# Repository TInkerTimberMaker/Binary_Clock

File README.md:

# Arduino Binary Clock (3× 74HC595 + DS3231)

A friendly, buildable binary‑coded decimal (BCD) clock for the Arduino Nano. It drives **three chained 74HC595 shift registers** in **sink mode** to show **hours, minutes, seconds**. A **DS3231 RTC** provides accurate timekeeping; two buttons set the time; a pot on **A1** controls global brightness via PWM on **D6**.

---
## Features
- **Time display**: Shows hours (00–23), minutes (00–59), seconds (00–59)
- **Accurate time** via DS3231 RTC (±2 ppm typical)
- **Packed BCD display**: tens and ones shown separately for Hours, Minutes, and Seconds
- **Brightness knob**: analog pot (A1) → PWM on OĒ (D6)
- **Set time**: Two buttons increment **minutes (D4)** and **hours (D3)**
- **Startup animation** if the RTC reports lost power (until a button press)
- **Low overhead**: loop updates only when the second changes; prints `HH:MM:SS  — CPU Work: xxxxµs` over Serial @ 9600 baud
- **Serial debug**: Prints `HH:MM:SS` on USB serial at 9600 baud

---
## Hardware Required
- Arduino Nano (or any 5 V Arduino)
- 3 × 74HC595N shift‑register chips
- DS3231 RTC module
- LEDs × 20 (6 hr + 7 min + 7 sec)
- Resistors (~470 Ω) × 20
- 1000µF electrolytic cap
- 2 × momentary pushbuttons
- Breadboard/wiring, Perfboard and hook up wires, or PCB

> **Sink mode** means LED anodes go to **+5 V** through a resistor and the HC595 outputs **pull low** to light the LED. That’s why the sketch inverts the BCD bits.

---
## Wiring

### Arduino ↔ 74HC595 chain

**Chain the data:** Arduino drives the **first** HC595’s SER; then **Q7′ (pin 9)** of each chip feeds the **next** chip’s SER.

| Connection                     | HC595 #1       | HC595 #2                              | HC595 #3                              |
| ------------------------------ | -------------- | ------------------------------------- | ------------------------------------- |
| **D11 → SER (data)**           | Pin 14         | *(from #1 Q7′ pin 9 → #2 SER pin 14)* | *(from #2 Q7′ pin 9 → #3 SER pin 14)* |
| **D12 → SH\_CP (shift clock)** | Pin 11         | Pin 11                                | Pin 11                                |
| **D8  → ST\_CP (latch)**       | Pin 12         | Pin 12                                | Pin 12                                |
| **D6  → OĒ (PWM brightness)** | Pin 13         | Pin 13                                | Pin 13                                |
| **+5 V → SRCLR̄**              | Pin 10         | Pin 10                                | Pin 10                                |
| **+5 V / GND**                 | Pin 16 / Pin 8 | Pin 16 / Pin 8                        | Pin 16 / Pin 8                        |

> If you don’t need brightness control, you may tie **OĒ (pin 13) to GND**. With dimming, keep OĒ on **D6 (PWM)**.

### RTC (DS3231)

| RTC Pin | Arduino                                                           |
| ------- | ----------------------------------------------------------------- |
| VCC     | +3.3 V                                                            |
| GND     | GND                                                               |
| SDA     | A4                                                                |
| SCL     | A5                                                                |
| SQW     | *(optional)* D2 (for 1 Hz interrupt; not required in this sketch) |

### LED mapping (sink‑mode)

Each LED: **+5 V → resistor → LED anode → LED cathode → Qx** on the HC595.

- **Seconds** (HC595 #1):
  - Ones: Q0 (1), Q1 (2), Q2 (4), Q3 (8)
  - Tens: Q4 (10), Q5 (20), Q6 (40)
- **Minutes** (HC595 #2): same bit layout as seconds
- **Hours**   (HC595 #3):
  - Ones: Q0 (1), Q1 (2), Q2 (4), Q3 (8)
  - Tens: Q4 (10)

> Bits Q7 are unused in this layout; you can repurpose them for a colon or status LED.

### Buttons (active‑LOW using internal pull‑ups)

| Arduino | Function  |
| ------- | --------- |
| D4      | Minutes ↑ |
| D3      | Hours ↑   |

Wire one side of each button to the Arduino pin above, the other side to **GND**.

---
## Software

- **IDE:** Arduino IDE (or Arduino CLI)
- **Libraries:** `RTClib` (Adafruit) — install via **Library Manager**

### Upload

1. Open the sketch in the IDE.
2. Select **Board: Arduino Nano** and the correct **Port**.
3. `Tools → Processor` → choose your Nano’s bootloader if needed (Old/New).
4. Upload. Open **Serial Monitor** @ 9600 baud to see time + CPU microseconds.

### How it works

- The loop calls `rtc.now()` and **only updates the LEDs when the second changes**.
- `packBCD()` converts decimal to packed BCD; the bytes are **inverted** because 0 = LED ON in sink mode.
- Data are shifted **MSBFIRST**: seconds → minutes → hours; latch toggles once per update.
- Pressing the buttons constructs a new `DateTime` with the hour/minute incremented and writes it back with `rtc.adjust()`.
- `updateBrightness()` reads A1 and PWM‑drives OĒ on D6 to dim the whole display.

---

## Examples

At **00:00:00** (all off):

```
Sec  tens: 000
Sec  ones: 0000
Min  tens: 000
Min  ones: 0000
Hour tens: 0
Hour ones: 0000
```

At **12:34:56**:

```
Seconds: tens=5 → Q5+Q4  | ones=6 → Q2+Q1
Minutes: tens=3 → Q5+Q4  | ones=4 → Q2
Hours:   tens=1 → Q4     | ones=2 → Q1
```

At **23:59:59**:

```
Seconds: tens=5 → Q5+Q4  | ones=9 → Q3+Q0
Minutes: tens=5 → Q5+Q4  | ones=9 → Q3+Q0
Hours:   tens=2 → Q4+Q?* | ones=3 → Q1+Q0
```

\*Note: hours tens never exceeds 2; only Q4 (10) will typically be used. If you wire extra bits for hours tens, leave them unconnected or ignore them.

---

## Troubleshooting

- **All LEDs on:** OĒ (pin 13) stuck HIGH or not connected; in sink mode, remember the sketch inverts bits.
- **Nothing updates:** Check **D11/D12/D8** and the Q7′ chaining (pin 9 → next SER pin 14).
- **Random flicker:** Add decouplers (0.1 µF per HC595) + a bulk cap (220-1000 µF) on 5 V.
- **Wrong digit order:** Verify you kept **MSBFIRST** and the LED bit mapping matches your panel.
- **Time won’t hold:** Make sure the RTC’s **CR2032** battery is installed; if the RTC lost power the sketch will show the startup animation until a button press.

---

## Optional: 1 Hz interrupt

You can wire DS3231 **SQW → D2** and attach an interrupt to update the display exactly on each rising/falling edge. It’s not required (the sketch polls `rtc.now()`), but it can reduce I²C traffic and jitter.  This is not implemented in this code.

---

## License

**© 2025 Tinker & Timber** — This project is licensed under **CC BY‑SA 4.0** and provided **“as‑is”** without warranty. You may copy, modify, and redistribute under the same terms, provided this notice remains intact.

[https://creativecommons.org/licenses/by-sa/4.0/](https://creativecommons.org/licenses/by-sa/4.0/)

---

Made with ♥ by Tinker & Timber

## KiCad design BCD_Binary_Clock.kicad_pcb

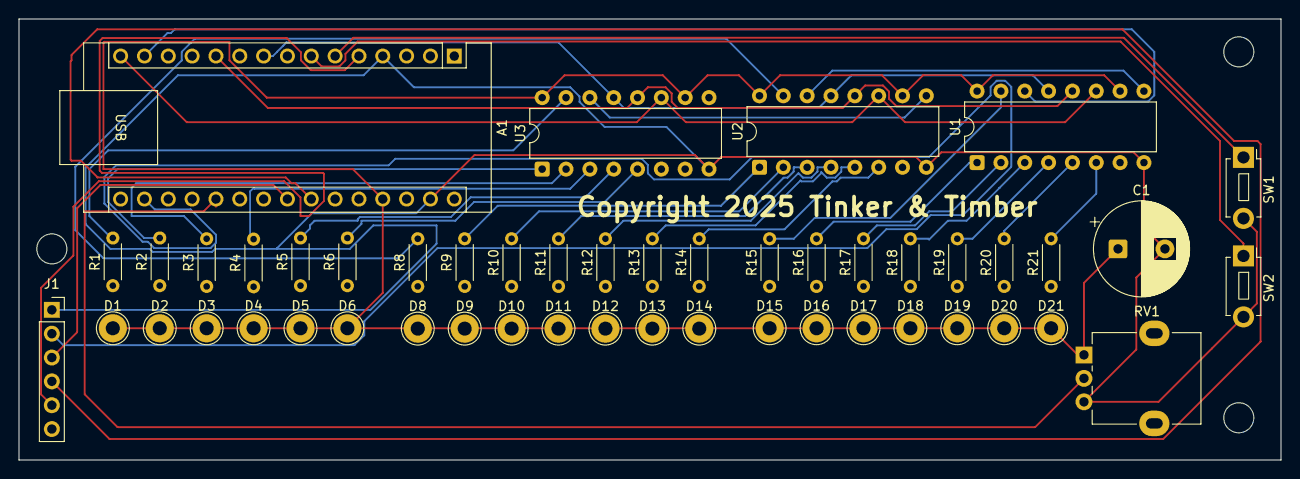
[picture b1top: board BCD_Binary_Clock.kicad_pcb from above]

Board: 2 copper layers, 134.5 x 47.0 mm, 52 parts (0 on the bottom side), 35 nets.

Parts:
A1: Arduino Nano; Arduino_Nano
C1: 1000uF; CP_Radial_D10.0mm_P5.00mm
D1, D2, D3, D4, D5, D6, D8, D9, D10, D11, D12, D13, D14, D15, D16, D17, D18, D19, D20, D21: LED; TestPoint_THTPad_D3.0mm_Drill1.5mm
J1: PinSocket_1x06_P2.54mm_Vertical
Mount: MountingHole_3.2mm_M3
Mount#2, Mount#3: MountingHole_3.2mm_M3
R1, R2, R3, R4, R5, R6, R8, R9, R10, R11, R12, R13, R14, R15, R16, R17, R18, R19, R20, R21: 470Ω; R_Axial_DIN0204_L3.6mm_D1.6mm_P5.08mm_Horizontal
RV1: Brightness Pot; Potentiometer_Alpha_RD901F-40-00D_Single_Vertical
SW1: HRS BUTTON; SW_PUSH_1P1T_6x3.5mm_H4.3_APEM_MJTP1243
SW2: MIN BUTTON; SW_PUSH_1P1T_6x3.5mm_H4.3_APEM_MJTP1243
U1, U2, U3: 74HC595; DIP-16_W7.62mm

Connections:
GND: A1.4 (GND), A1.29 (GND), C1.2, J1.1, RV1.3, SW1.2, SW2.2, U1.8 (GND), U2.8 (GND), U3.8 (GND)
unnamed: A1.17 (3V3), J1.2
unnamed: A1.20 (A1), RV1.2
unnamed: A1.23 (A4), J1.3
unnamed: A1.24 (A5), J1.4
unnamed: A1.5 (D2), J1.5
unnamed: A1.6 (D3), SW1.1
unnamed: A1.7 (D4), SW2.1
unnamed: A1.9 (D6), U1.13 (~OE), U2.13 (~OE), U3.13 (~OE)
unnamed: A1.11 (D8), U1.12 (RCLK), U2.12 (RCLK), U3.12 (RCLK)
unnamed: A1.14 (D11), U1.14 (SER)
unnamed: A1.15 (D12), U1.11 (SRCLK), U2.11 (SRCLK), U3.11 (SRCLK)
unnamed: R15.2, U1.15 (QA)
unnamed: R16.2, U1.1 (QB)
unnamed: R17.2, U1.2 (QC)
unnamed: R18.2, U1.3 (QD)
unnamed: R19.2, U1.4 (QE)
unnamed: R20.2, U1.5 (QF)
unnamed: R21.2, U1.6 (QG)
unnamed: U1.9 (QH'), U2.14 (SER)
unnamed: R8.2, U2.15 (QA)
unnamed: R9.2, U2.1 (QB)
unnamed: R10.2, U2.2 (QC)
unnamed: R11.2, U2.3 (QD)
unnamed: R12.2, U2.4 (QE)
unnamed: R13.2, U2.5 (QF)
unnamed: R14.2, U2.6 (QG)
unnamed: U2.9 (QH'), U3.14 (SER)
unnamed: R1.2, U3.15 (QA)
unnamed: R2.2, U3.1 (QB)
unnamed: R3.2, U3.2 (QC)
unnamed: R4.2, U3.3 (QD)
unnamed: R5.2, U3.4 (QE)
unnamed: R6.2, U3.5 (QF)
VCC: A1.27 (+5V), C1.1, D1.1 (K), D2.1 (K), D3.1 (K), D4.1 (K), D5.1 (K), D6.1 (K), D8.1 (K), D9.1 (K), D10.1 (K), D11.1 (K), D12.1 (K), D13.1 (K), D14.1 (K), D15.1 (K), D16.1 (K), D17.1 (K), D18.1 (K), D19.1 (K), D20.1 (K), D21.1 (K), RV1.1, U1.10 (~SRCLR), U1.16 (VCC), U2.10 (~SRCLR), U2.16 (VCC), U3.10 (~SRCLR), U3.16 (VCC)

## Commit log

2025-08-12 Drilling Template for LED panel
2025-08-12 PCB Gerber Files
    Use to get your own PCBs made
2025-08-12 KiCAD Circuit Schematic
2025-08-12 KiCAD PCB Layout
2025-08-12 Binary Clock Arduino Code v1.0
2025-08-16 Fixed SW1 & SW2 going to VCC - now pulling to GNC
2025-08-17 Added STLs for case (full & minimal versions)
2025-08-19 Updated Gerbers to pull switches to GND not VCC

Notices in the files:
BCD_Binary_Clock.kicad_pcb:
Copyright 2025 Tinker & Timber
